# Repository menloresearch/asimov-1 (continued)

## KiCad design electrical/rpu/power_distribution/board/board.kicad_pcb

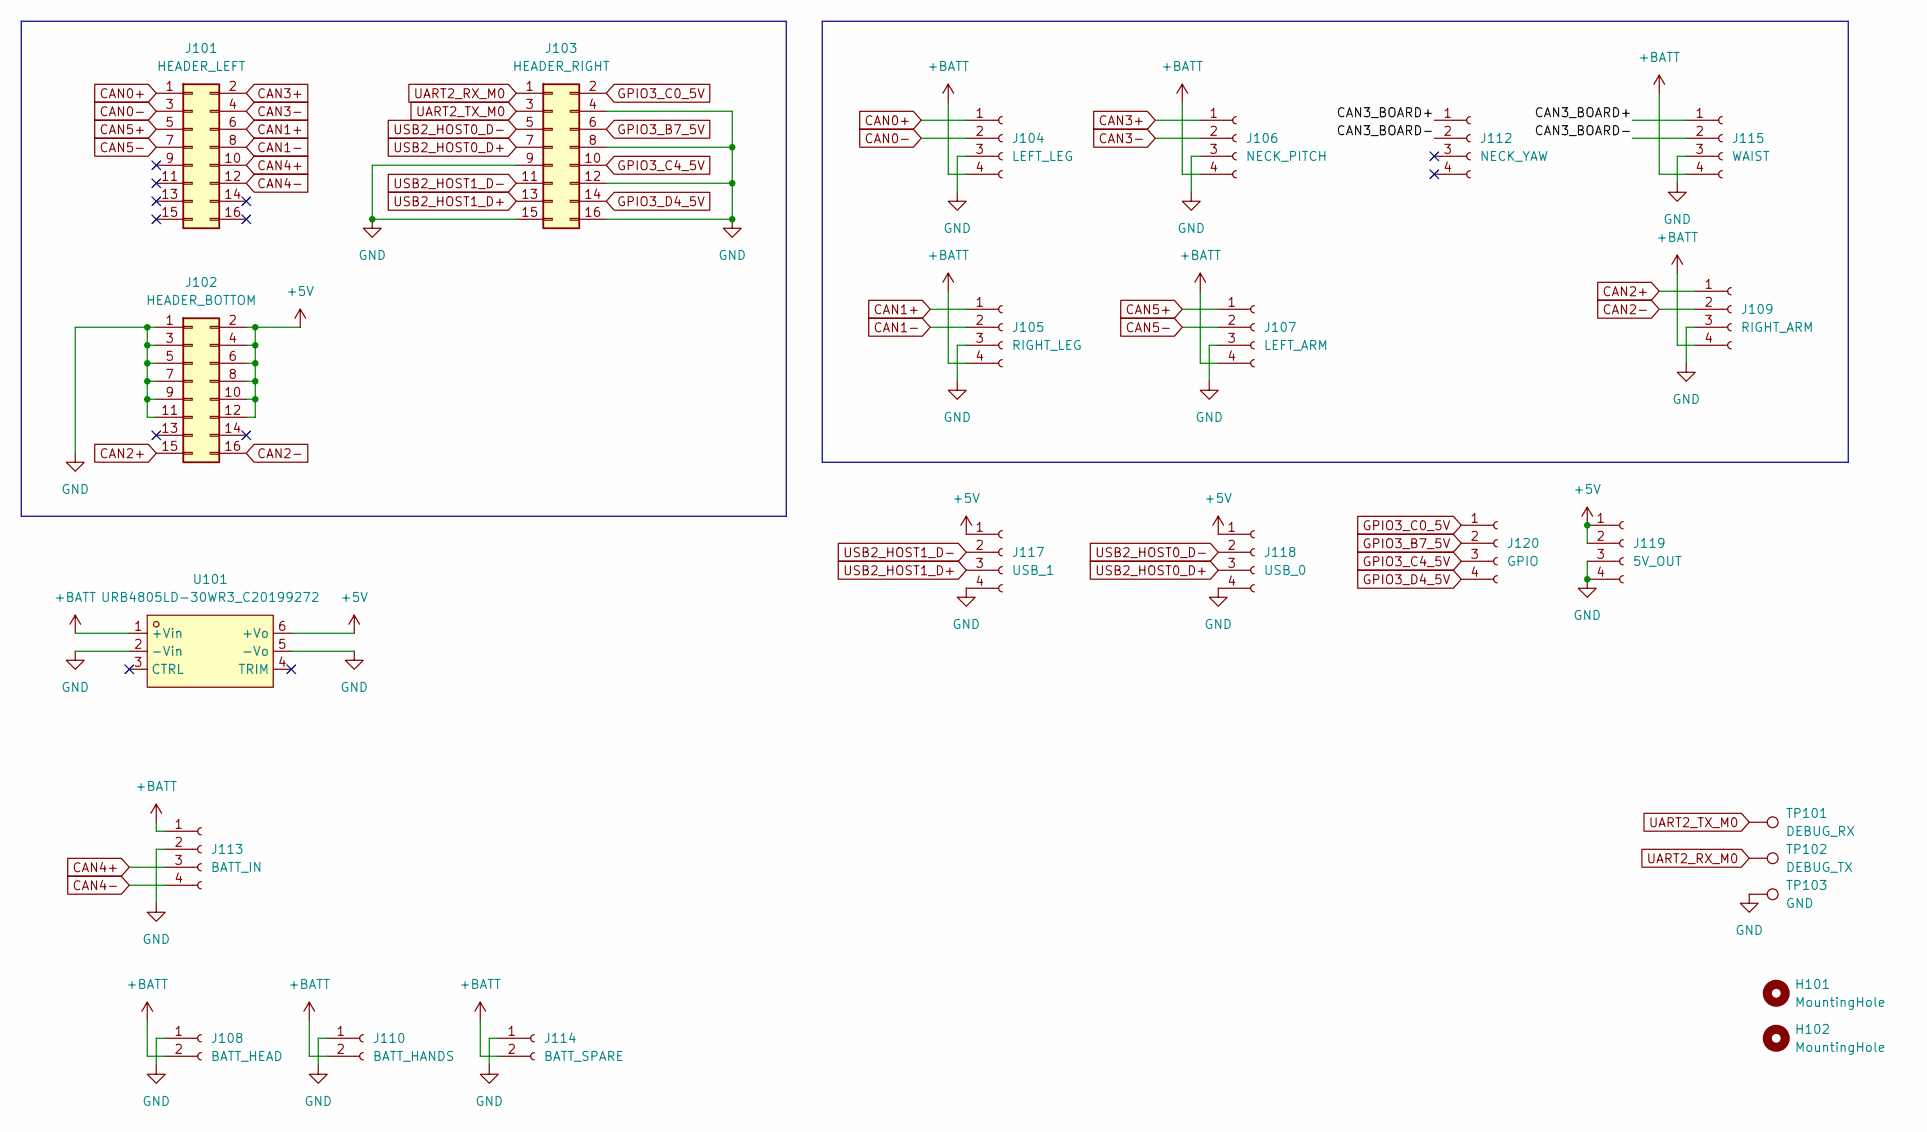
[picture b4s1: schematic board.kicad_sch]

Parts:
H101, H102: MountingHole; MountingHole_3.2mm_M3
J101: HEADER_LEFT; PinSocket_2x08_P2.54mm_Vertical; LCSC C30734
J102: HEADER_BOTTOM; PinSocket_2x08_P2.54mm_Vertical; LCSC C30734
J103: HEADER_RIGHT; PinSocket_2x08_P2.54mm_Vertical; LCSC C30734
J104: LEFT_LEG; CONN-TH_XT30PB-M
J105: RIGHT_LEG; CONN-TH_XT30PB-M
J106: NECK_PITCH; CONN-TH_XT30PB-M
J107: LEFT_ARM; CONN-TH_XT30PB-M
J108: BATT_HEAD; AMASS_XT30UPB-F_1x02_P5.0mm_Vertical; LCSC C108769
J109: RIGHT_ARM; CONN-TH_XT30PB-M
J110: BATT_HANDS; AMASS_XT30UPB-F_1x02_P5.0mm_Vertical; LCSC C108769
J112: NECK_YAW; CONN-TH_XT30PB-M
J113: BATT_IN; CONN-SMD_XT90-2-2-PB-MGY; LCSC C19268046
J114: BATT_SPARE; AMASS_XT30UPB-F_1x02_P5.0mm_Vertical; LCSC C108769
J115: WAIST; CONN-TH_XT30PB-M
J117: USB_1; JST_XH_B4B-XH-A_1x04_P2.50mm_Vertical; LCSC C144395
J118: USB_0; JST_XH_B4B-XH-A_1x04_P2.50mm_Vertical; LCSC C144395
J119: 5V_OUT; JST_XH_B4B-XH-A_1x04_P2.50mm_Vertical; LCSC C144395
J120: GPIO; JST_XH_B4B-XH-A_1x04_P2.50mm_Vertical; LCSC C144395
TP101: DEBUG_RX; TestPoint_Pad_D1.0mm
TP102: DEBUG_TX; TestPoint_Pad_D1.0mm
TP103: GND; TestPoint_Pad_D1.0mm
U101: URB4805LD-30WR3_C20199272; PWRM-TH_TURBXXXXLD-30WR3; MPN URB4805LD-30WR3; LCSC Part C20199272

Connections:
+5V: J102.2, J102.4, J102.6, J102.8, J102.10, J102.12, J117.1, J118.1, J119.1, J119.2, U101.6 (+Vo)
+BATT: J104.4, J105.4, J106.4, J107.4, J108.2, J109.4, J110.2, J113.1, J114.2, J115.4, U101.1 (+Vin)
/CAN3_BOARD+: J112.1, J115.1
/CAN3_BOARD-: J112.2, J115.2
CAN0+: J101.1, J104.1
CAN0-: J101.3, J104.2
CAN1+: J101.6, J105.1
CAN1-: J101.8, J105.2
CAN2+: J102.15, J109.1
CAN2-: J102.16, J109.2
CAN3+: J101.2, J106.1
CAN3-: J101.4, J106.2
CAN4+: J101.10, J113.3
CAN4-: J101.12, J113.4
CAN5+: J101.5, J107.1
CAN5-: J101.7, J107.2
GND: J102.1, J102.3, J102.5, J102.7, J102.9, J102.11, J103.4, J103.8, J103.9, J103.12, J103.15, J103.16, J104.3, J105.3, J106.3, J107.3, J108.1, J109.3, J110.1, J113.2, J114.1, J115.3, J117.4, J118.4, J119.3, J119.4, TP103.1 (1_1), U101.2 (-Vin), U101.5 (-Vo)
GPIO3_B7_5V: J103.6, J120.2
GPIO3_C0_5V: J103.2, J120.1
GPIO3_C4_5V: J103.10, J120.3
GPIO3_D4_5V: J103.14, J120.4
UART2_RX_M0: J103.1, TP102.1 (1_1)
UART2_TX_M0: J103.3, TP101.1 (1_1)
USB2_HOST0_D+: J103.7, J118.3
USB2_HOST0_D-: J103.5, J118.2
USB2_HOST1_D+: J103.13, J117.3
USB2_HOST1_D-: J103.11, J117.2

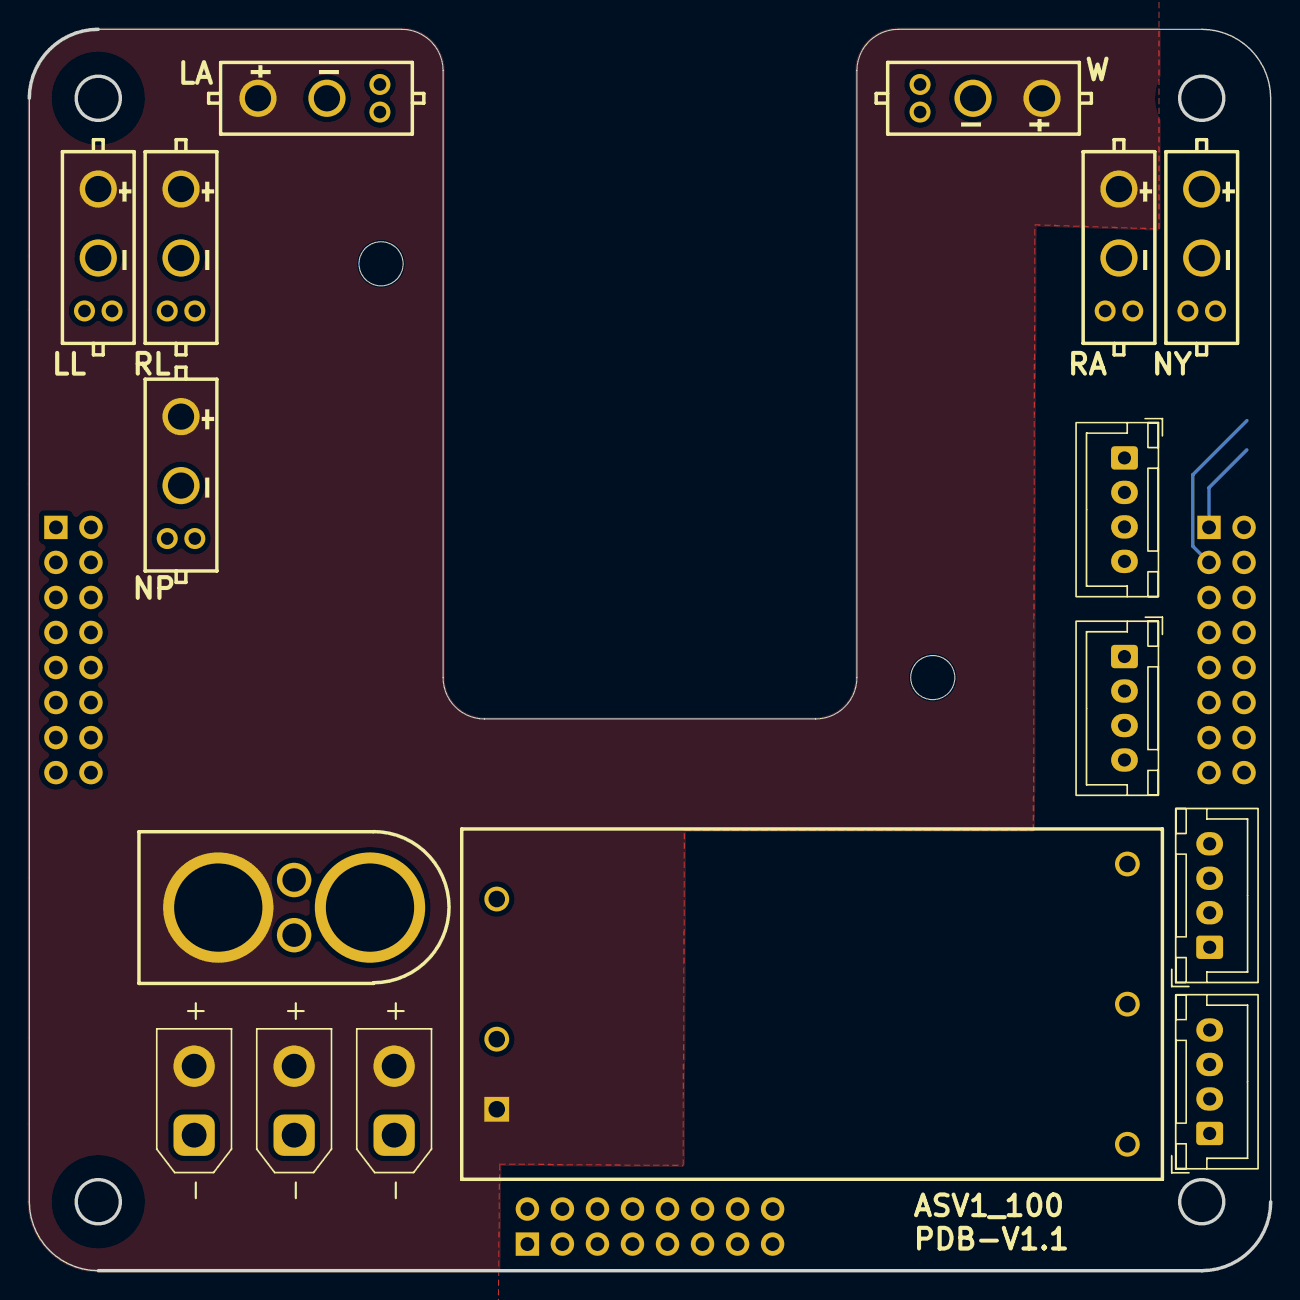
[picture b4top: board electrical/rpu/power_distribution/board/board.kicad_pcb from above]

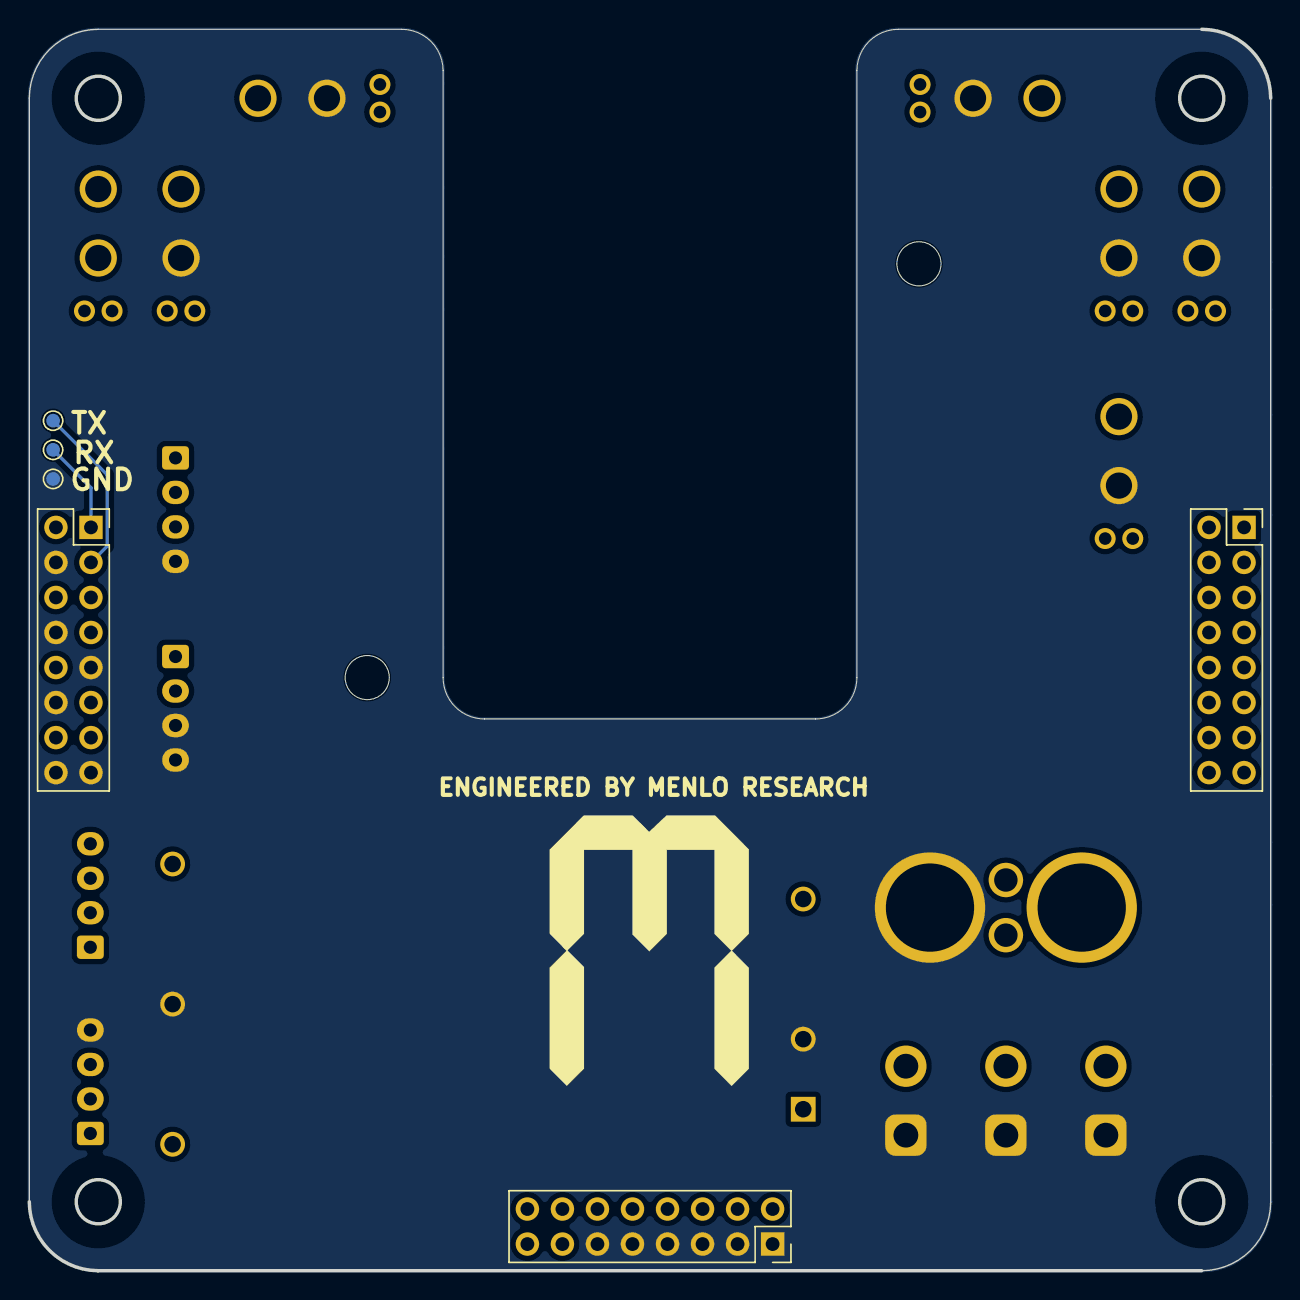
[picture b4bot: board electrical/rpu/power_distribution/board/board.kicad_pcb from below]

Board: 4 copper layers, 90.0 x 90.0 mm, 24 parts (6 on the bottom side), 27 nets.
